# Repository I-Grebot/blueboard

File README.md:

# BlueBoard v1

The BlueBoard is a small form-factor "all-in-one" electronic board for 2 wheels robots.

## Features

The board features the following items:

* Compact size: 10 cm x 10 cm
* Single input power-supply (+14V min)
* Integrated Power-Supplies for logic domains using efficient DC/DC step-down regulators:
 * +12V/1A (industrial sensors)
 * +5V/1A (quadrature encoders, other 5V logic)
 * +3/3V/1A (most of digital logic)
* Integrated  Power-Supplies for heavy loads:
 * +12V/3A (generic purpose)
 * +7.4V/3A (dynamixel digital servos ~ can be adjusted)
 * +5V/3A (analog servos)
* Secure and robust Power-pack connector
* Main ON/OFF + Emergency switch connectors
* 2x Full H-Bridge output controls for DRV8842 (2.5A)
* 8x Opto-coupled analog-servos interface (PWM)
* 2x Connectors + 1x terminal for XL-320 digital servos interface
* 2x Quadrature encoders inputs
* 10x Opto-coupled Industrial sensor inputs (NPN/PNP  types selectable)
* 8x Digital Inputs
* RS485 connector for sensor-bus (to be used with ProxTof boards or other)
* UART with RTS/CTS signals
* USB 2.0 OTG connector
* ST-Link with SWD + SWO programming / debugging connector
* Expander connector (to be used with microBoard_HMI):
 * 1x SPI
 * 1x CAN
 * 6x Digital inputs (user selections switches)
 * 1x Digital outputs 

## Troubleshooting

* Mimimum input voltage (TEN / PTN modules) is high for 4S batteries (error due to 6S -> 4S design migration)
* Not working 4S battery cell monitoring analog circuit (to be further checked)

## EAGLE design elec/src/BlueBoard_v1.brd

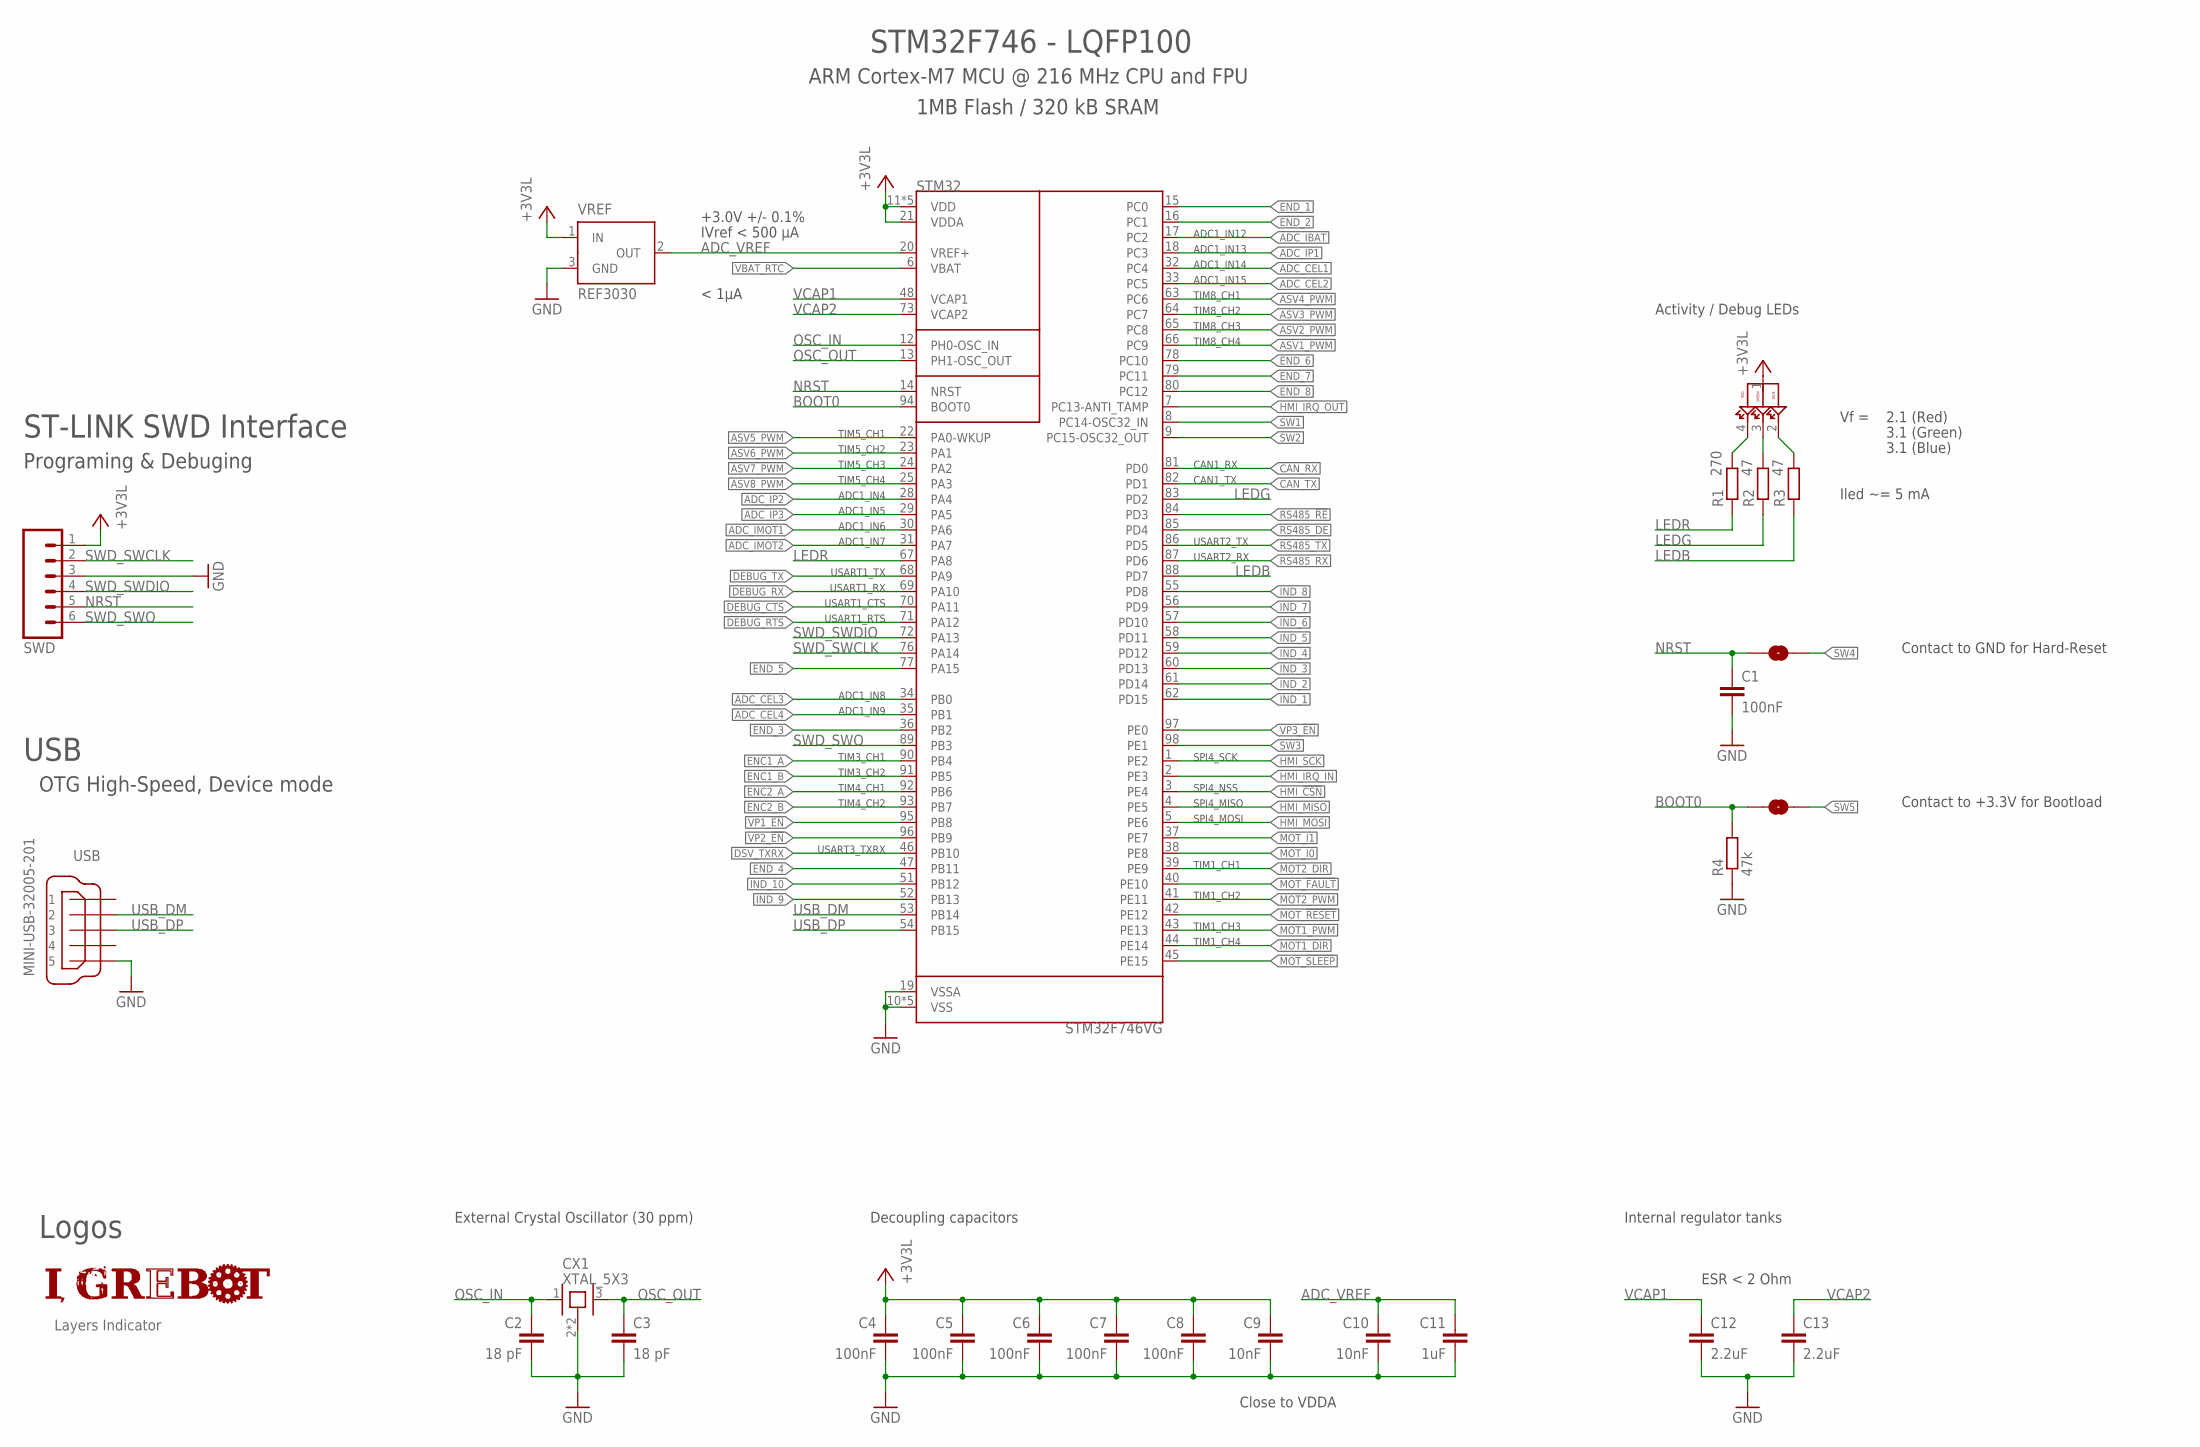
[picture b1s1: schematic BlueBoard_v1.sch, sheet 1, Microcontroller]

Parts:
C1, C4, C5, C6, C7, C8: 100nF; C0603
C2, C3: 18 pF; C0603
C9, C10: 10nF; C0603
C11: 1uF; C0805
C12, C13: 2.2uF; C0805
CX1: XTAL_5X3; CRYSTAL-OSC-SMD-5X3
LED1: ASMB-MTB0-0A3A2; PLCC4
LOGO_IGREBOT: LOGO_IGREBOT12X2MM; IGREBOT_12X2MM
LOGO_LAYERS: LAYERS_CHECK4_LAYERS; LAYERS_CHECK_4
R1: 270; R0603
R2, R3: 47; R0603
R4: 47k; R0603
SJ1, SJ2: SOLDERJUMPERNC2; SJ_2S-NOTRACE
STM32: STM32F746VG; LQFP_100
SWD: M06LOCK; 1X06_LOCK
USB: MINI-USB-32005-201; 32005-201
VREF: REF3030; SOT23

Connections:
+3V3L: C4.1, C5.1, C6.1, C7.1, C8.1, C9.1, LED1.1 (A), STM32.11 (VDD), STM32.21 (VDDA), STM32.27 (VDD), STM32.50 (VDD), STM32.75 (VDD), STM32.100 (VDD), SWD.1, VREF.1 (IN); also elsewhere on the board
ADC_CEL1: STM32.32 (PC4); also elsewhere on the board
ADC_CEL2: STM32.33 (PC5); also elsewhere on the board
ADC_CEL3: STM32.34 (PB0); also elsewhere on the board
ADC_CEL4: STM32.35 (PB1); also elsewhere on the board
ADC_IBAT: STM32.17 (PC2); also elsewhere on the board
ADC_IMOT1: STM32.30 (PA6); also elsewhere on the board
ADC_IMOT2: STM32.31 (PA7); also elsewhere on the board
ADC_IP1: STM32.18 (PC3); also elsewhere on the board
ADC_IP2: STM32.28 (PA4); also elsewhere on the board
ADC_IP3: STM32.29 (PA5); also elsewhere on the board
ADC_VREF: C10.1, C11.1, STM32.20 (VREF+), VREF.2 (OUT)
ASV1_PWM: STM32.66 (PC9); also elsewhere on the board
ASV2_PWM: STM32.65 (PC8); also elsewhere on the board
ASV3_PWM: STM32.64 (PC7); also elsewhere on the board
ASV4_PWM: STM32.63 (PC6); also elsewhere on the board
ASV5_PWM: STM32.22 (PA0-WKUP); also elsewhere on the board
ASV6_PWM: STM32.23 (PA1); also elsewhere on the board
ASV7_PWM: STM32.24 (PA2); also elsewhere on the board
ASV8_PWM: STM32.25 (PA3); also elsewhere on the board
BOOT0: R4.2, SJ2.1, STM32.94 (BOOT0)
CAN_RX: STM32.81 (PD0); also elsewhere on the board
CAN_TX: STM32.82 (PD1); also elsewhere on the board
DEBUG_CTS: STM32.70 (PA11); also elsewhere on the board
DEBUG_RTS: STM32.71 (PA12); also elsewhere on the board
DEBUG_RX: STM32.69 (PA10); also elsewhere on the board
DEBUG_TX: STM32.68 (PA9); also elsewhere on the board
DSV_TXRX: STM32.46 (PB10); also elsewhere on the board
ENC1_A: STM32.90 (PB4); also elsewhere on the board
ENC1_B: STM32.91 (PB5); also elsewhere on the board
ENC2_A: STM32.92 (PB6); also elsewhere on the board
ENC2_B: STM32.93 (PB7); also elsewhere on the board
END_1: STM32.15 (PC0); also elsewhere on the board
END_2: STM32.16 (PC1); also elsewhere on the board
END_3: STM32.36 (PB2); also elsewhere on the board
END_4: STM32.47 (PB11); also elsewhere on the board
END_5: STM32.77 (PA15); also elsewhere on the board
END_6: STM32.78 (PC10); also elsewhere on the board
END_7: STM32.79 (PC11); also elsewhere on the board
END_8: STM32.80 (PC12); also elsewhere on the board
GND: C1.2, C2.2, C3.2, C4.2, C5.2, C6.2, C7.2, C8.2, C9.2, C10.2, C11.2, C12.2, C13.2, CX1.2, CX1.4, R4.1, STM32.10 (VSS), STM32.19 (VSSA), STM32.26 (VSS), STM32.49 (VSS), STM32.74 (VSS), STM32.99 (VSS), SWD.3, USB.5, VREF.3 (GND); also elsewhere on the board
HMI_!CSN!: STM32.3 (PE4); also elsewhere on the board
HMI_IRQ_IN: STM32.2 (PE3); also elsewhere on the board
HMI_IRQ_OUT: STM32.7 (PC13-ANTI_TAMP); also elsewhere on the board
HMI_MISO: STM32.4 (PE5); also elsewhere on the board
HMI_MOSI: STM32.5 (PE6); also elsewhere on the board
HMI_SCK: STM32.1 (PE2); also elsewhere on the board
IND_1: STM32.62 (PD15); also elsewhere on the board
IND_2: STM32.61 (PD14); also elsewhere on the board
IND_3: STM32.60 (PD13); also elsewhere on the board
IND_4: STM32.59 (PD12); also elsewhere on the board
IND_5: STM32.58 (PD11); also elsewhere on the board
IND_6: STM32.57 (PD10); also elsewhere on the board
IND_7: STM32.56 (PD9); also elsewhere on the board
IND_8: STM32.55 (PD8); also elsewhere on the board
IND_9: STM32.52 (PB13); also elsewhere on the board
IND_10: STM32.51 (PB12); also elsewhere on the board
LEDB: R3.1, STM32.88 (PD7)
LEDG: R2.1, STM32.83 (PD2)
LEDR: R1.1, STM32.67 (PA8)
MOT1_DIR: STM32.44 (PE14); also elsewhere on the board
MOT1_PWM: STM32.43 (PE13); also elsewhere on the board
MOT2_DIR: STM32.39 (PE9); also elsewhere on the board
MOT2_PWM: STM32.41 (PE11); also elsewhere on the board
MOT_!FAULT!: STM32.40 (PE10); also elsewhere on the board
MOT_!RESET!: STM32.42 (PE12); also elsewhere on the board
MOT_!SLEEP!: STM32.45 (PE15); also elsewhere on the board
MOT_I0: STM32.38 (PE8); also elsewhere on the board
MOT_I1: STM32.37 (PE7); also elsewhere on the board
unnamed: LED1.4 (CR), R1.2
unnamed: LED1.3 (CG), R2.2
unnamed: LED1.2 (CB), R3.2
NRST: C1.1, SJ1.1, STM32.14 (NRST), SWD.5
OSC_IN: C2.1, CX1.1, STM32.12 (PH0-OSC_IN)
OSC_OUT: C3.1, CX1.3, STM32.13 (PH1-OSC_OUT)
RS485_!RE!: STM32.84 (PD3); also elsewhere on the board
RS485_DE: STM32.85 (PD4); also elsewhere on the board
RS485_RX: STM32.87 (PD6); also elsewhere on the board
RS485_TX: STM32.86 (PD5); also elsewhere on the board
SW1: STM32.8 (PC14-OSC32_IN); also elsewhere on the board
SW2: STM32.9 (PC15-OSC32_OUT); also elsewhere on the board
SW3: STM32.98 (PE1); also elsewhere on the board
SW4: SJ1.2; also elsewhere on the board
SW5: SJ2.2; also elsewhere on the board
SWD_SWCLK: STM32.76 (PA14), SWD.2
SWD_SWDIO: STM32.72 (PA13), SWD.4
SWD_SWO: STM32.89 (PB3), SWD.6
USB_DM: STM32.53 (PB14), USB.2
USB_DP: STM32.54 (PB15), USB.3
VBAT_RTC: STM32.6 (VBAT); also elsewhere on the board
VCAP1: C12.1, STM32.48 (VCAP1)
VCAP2: C13.1, STM32.73 (VCAP2)
VP1_!EN!: STM32.95 (PB8); also elsewhere on the board
VP2_!EN!: STM32.96 (PB9); also elsewhere on the board
VP3_!EN!: STM32.97 (PE0); also elsewhere on the board

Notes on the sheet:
Decoupling capacitors
ESR < 2 Ohm
< 1µA
TIM5_CH1
TIM5_CH2
TIM5_CH3
TIM5_CH4
USART1_TX
USART1_RX
USART1_CTS
USART1_RTS
TIM3_CH1
TIM3_CH2
TIM4_CH1
TIM4_CH2
USART3_TXRX
TIM1_CH4
TIM1_CH3
TIM1_CH2
TIM1_CH1
SPI4_MOSI
SPI4_MISO
SPI4_NSS
SPI4_SCK
USART2_RX
USART2_TX
CAN1_TX
CAN1_RX
TIM8_CH1
TIM8_CH2
TIM8_CH3
TIM8_CH4
USB
Programing & Debuging
ST-LINK SWD Interface
STM32F746 - LQFP100
ARM Cortex-M7 MCU @ 216 MHz CPU and FPU
1MB Flash / 320 kB SRAM
OTG High-Speed, Device mode
Internal regulator tanks

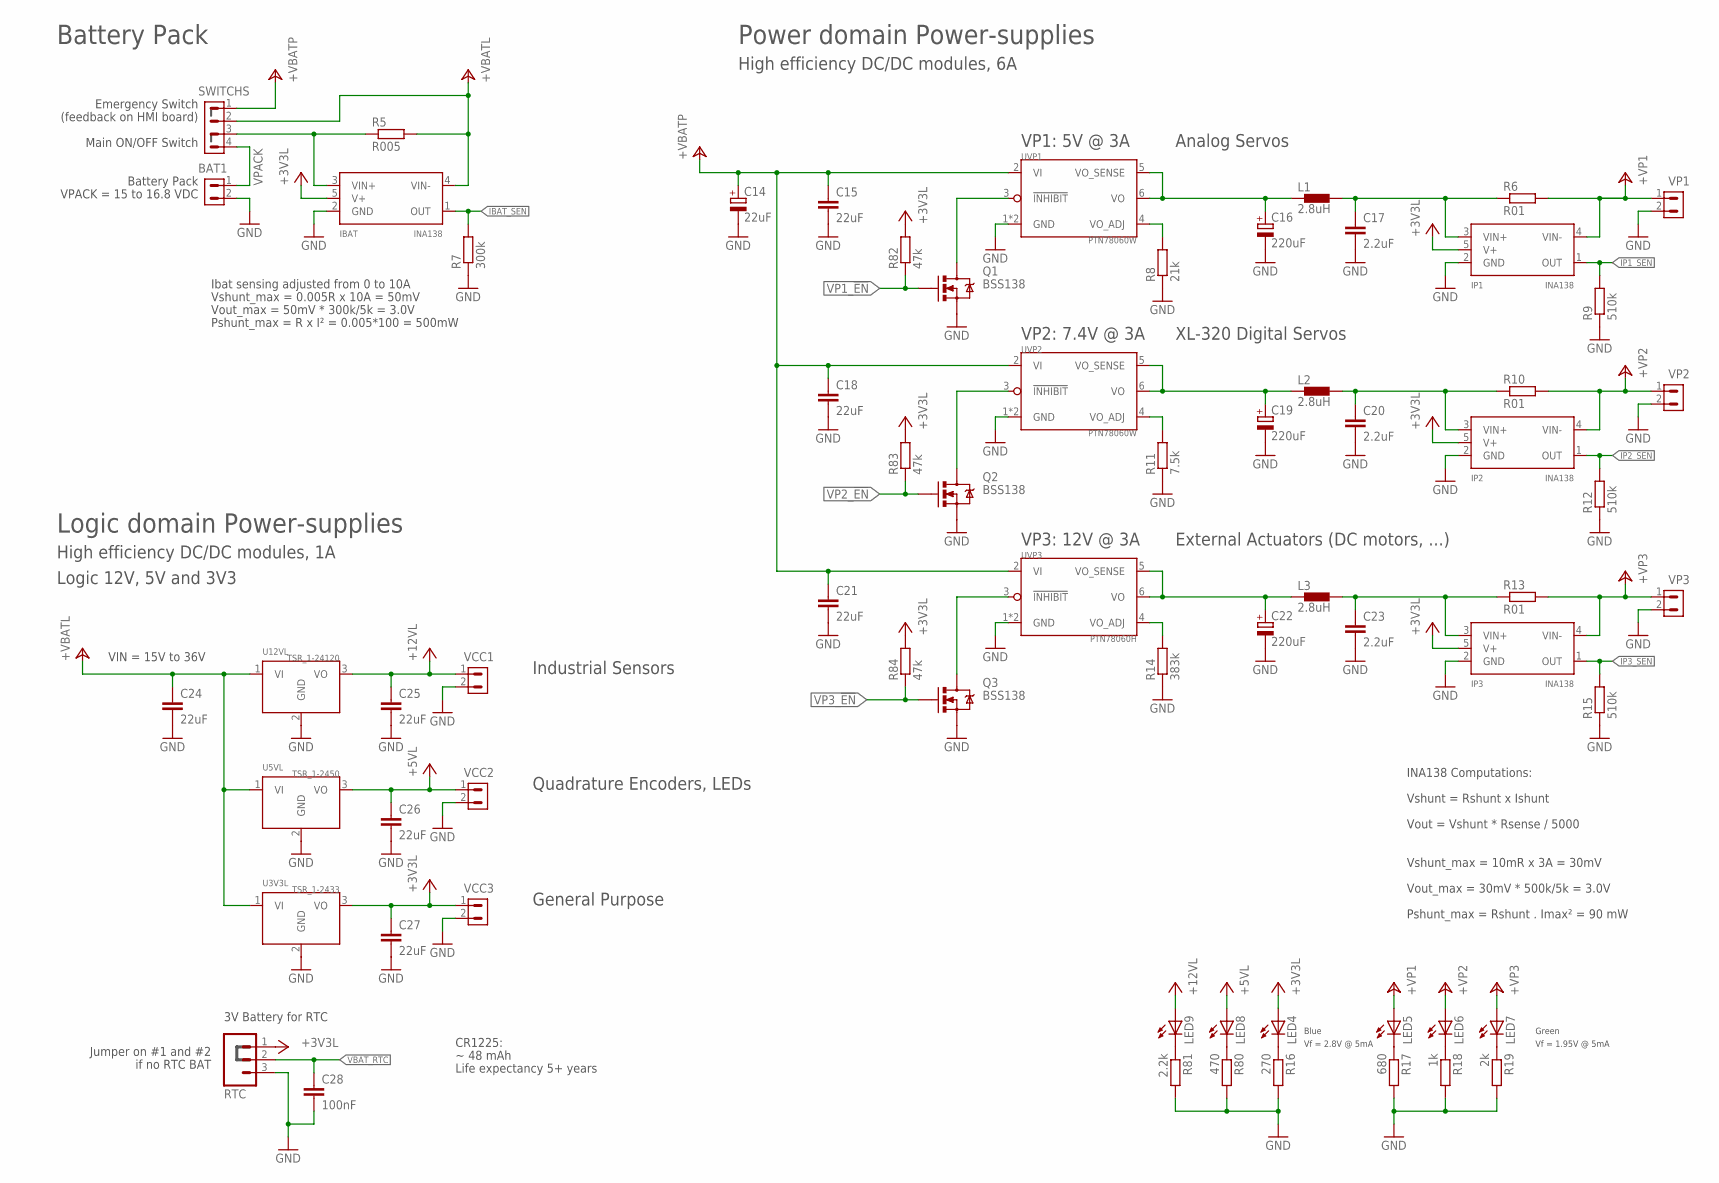
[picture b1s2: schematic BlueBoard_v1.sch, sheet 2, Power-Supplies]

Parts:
BAT1: MC15-GF-3.81-LR_2; CON_3.81_LR_2
C14: 22uF; PANASONIC_B
C15, C18, C21, C24: 22uF; C3225
C16, C19, C22: 220uF; PANASONIC_D
C17, C20, C23: 2.2uF; C3225
C25, C26, C27: 22uF; C1210
C28: 100nF; C0603
IBAT: INA138; DBV_05
IP1, IP2, IP3: INA138; DBV_05
L1, L2, L3: 2.8uH; DR1030
LED4, LED5, LED6, LED7, LED8, LED9: LEDCHIP-LED0805; CHIP-LED0805
Q1, Q2, Q3: BSS138; SOT23
R5: R005; R2512
R6, R10, R13: R01; R2512
R7: 300k; R0603
R8: 21k; R0603
R9, R12, R15: 510k; R0603
R11: 7.5k; R0603
R14: 383k; R0603
R16: 270; R0603
R17: 680; R0603
R18: 1k; R0603
R19: 2k; R0603
R80: 470; R0603
R81: 2.2k; R0603
R82, R83, R84: 47k; R0603
RTC: M03LOCK; 1X03_LOCK
SWITCHS: MC15-GF-3.81-LR_4; CON_3.81_LR_4
U3V3L: TSR_1-2433; TSR1
U5VL: TSR_1-2450; TSR1
U12VL: TSR_1-24120; TSR1
UVP1, UVP2: PTN78060W; PTN78060
UVP3: PTN78060H; PTN78060
VCC1, VCC2, VCC3: CON_3.5_2
VP1, VP2, VP3: CON_3.5_2

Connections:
!INHIBIT!_VP1: Q1.3 (D), UVP1.3 (!INHIBIT!)
!INHIBIT!_VP5: Q2.3 (D), UVP2.3 (!INHIBIT!)
!INHIBIT!_VP6: Q3.3 (D), UVP3.3 (!INHIBIT!)
+3V3L: C27.1, IBAT.5 (V+), IP1.5 (V+), IP2.5 (V+), IP3.5 (V+), LED4.A, R82.2, R83.2, R84.2, RTC.1, U3V3L.3 (VO), VCC3.1; also elsewhere on the board
+5VL: C26.1, LED8.A, U5VL.3 (VO), VCC2.1; also elsewhere on the board
+12VL: C25.1, LED9.A, U12VL.3 (VO), VCC1.1; also elsewhere on the board
+VBATL: C24.1, IBAT.4 (VIN-), R5.2, SWITCHS.2, U3V3L.1 (VI), U5VL.1 (VI), U12VL.1 (VI)
+VBATP: C14.+, C15.1, C18.1, C21.1, SWITCHS.1, UVP1.2 (VI), UVP2.2 (VI), UVP3.2 (VI); also elsewhere on the board
+VP1: IP1.4 (VIN-), LED5.A, R6.2, VP1.1; also elsewhere on the board
+VP2: IP2.4 (VIN-), LED6.A, R10.2, VP2.1; also elsewhere on the board
+VP3: IP3.4 (VIN-), LED7.A, R13.2, VP3.1
GND: BAT1.2, C14.-, C15.2, C16.-, C17.2, C18.2, C19.-, C20.2, C21.2, C22.-, C23.2, C24.2, C25.2, C26.2, C27.2, C28.2, IBAT.2 (GND), IP1.2 (GND), IP2.2 (GND), IP3.2 (GND), Q1.2 (S), Q2.2 (S), Q3.2 (S), R7.1, R8.1, R9.1, R11.1, R12.1, R14.1, R15.1, R16.2, R17.2, R18.2, R19.2, R80.2, R81.2, RTC.3, U3V3L.2 (GND), U5VL.2 (GND), U12VL.2 (GND), UVP1.1 (GND), UVP1.7 (GND), UVP2.1 (GND), UVP2.7 (GND), UVP3.1 (GND), UVP3.7 (GND), VCC1.2, VCC2.2, VCC3.2, VP1.2, VP2.2, VP3.2; also elsewhere on the board
IBAT_SEN: IBAT.1 (OUT), R7.2; also elsewhere on the board
IP1_SEN: IP1.1 (OUT), R9.2; also elsewhere on the board
IP2_SEN: IP2.1 (OUT), R12.2; also elsewhere on the board
IP3_SEN: IP3.1 (OUT), R15.2; also elsewhere on the board
unnamed: C16.+, L1.1, UVP1.5 (VO_SENSE), UVP1.6 (VO)
unnamed: C17.1, IP1.3 (VIN+), L1.2, R6.1
unnamed: R14.2, UVP3.4 (VO_ADJ)
unnamed: R11.2, UVP2.4 (VO_ADJ)
unnamed: C19.+, L2.1, UVP2.5 (VO_SENSE), UVP2.6 (VO)
unnamed: R8.2, UVP1.4 (VO_ADJ)
unnamed: C20.1, IP2.3 (VIN+), L2.2, R10.1
unnamed: C22.+, L3.1, UVP3.5 (VO_SENSE), UVP3.6 (VO)
unnamed: C23.1, IP3.3 (VIN+), L3.2, R13.1
unnamed: LED8.C, R80.1
unnamed: LED9.C, R81.1
unnamed: LED5.C, R17.1
unnamed: LED4.C, R16.1
unnamed: LED6.C, R18.1
unnamed: LED7.C, R19.1
unnamed: IBAT.3 (VIN+), R5.1, SWITCHS.3
VBAT_RTC: C28.1, RTC.2; also elsewhere on the board
VP1_!EN!: Q1.1 (G), R82.1; also elsewhere on the board
VP2_!EN!: Q2.1 (G), R83.1; also elsewhere on the board
VP3_!EN!: Q3.1 (G), R84.1; also elsewhere on the board
VPACK: BAT1.1, SWITCHS.4

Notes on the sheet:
VP1: 5V @ 3A
VP2: 7.4V @ 3A
Logic 12V, 5V and 3V3
VPACK = 15 to 16.8 VDC
Logic domain Power-supplies
High efficiency DC/DC modules, 1A
Power domain Power-supplies
High efficiency DC/DC modules, 6A
Battery Pack
Vshunt = Rshunt x Ishunt
Vout = Vshunt * Rsense / 5000
Vshunt_max = 10mR x 3A = 30mV
Vout_max = 30mV * 500k/5k = 3.0V
Emergency Switch
Main ON/OFF Switch
(feedback on HMI board)
Vshunt_max = 0.005R x 10A = 50mV
Vout_max = 50mV * 300k/5k = 3.0V
Ibat sensing adjusted from 0 to 10A
INA138 Computations:
Pshunt_max = R x I² = 0.005*100 = 500mW
Analog Servos
XL-320 Digital Servos
Industrial Sensors
General Purpose
Quadrature Encoders, LEDs
VP3: 12V @ 3A
External Actuators (DC motors, ...)
3V Battery for RTC
~ 48 mAh
Life expectancy 5+ years
Green
Blue
CR1225:
Pshunt_max = Rshunt . Imax² = 90 mW
Jumper on #1 and #2
if no RTC BAT
Vf = 2.8V @ 5mA
Vf = 1.95V @ 5mA
VIN = 15V to 36V

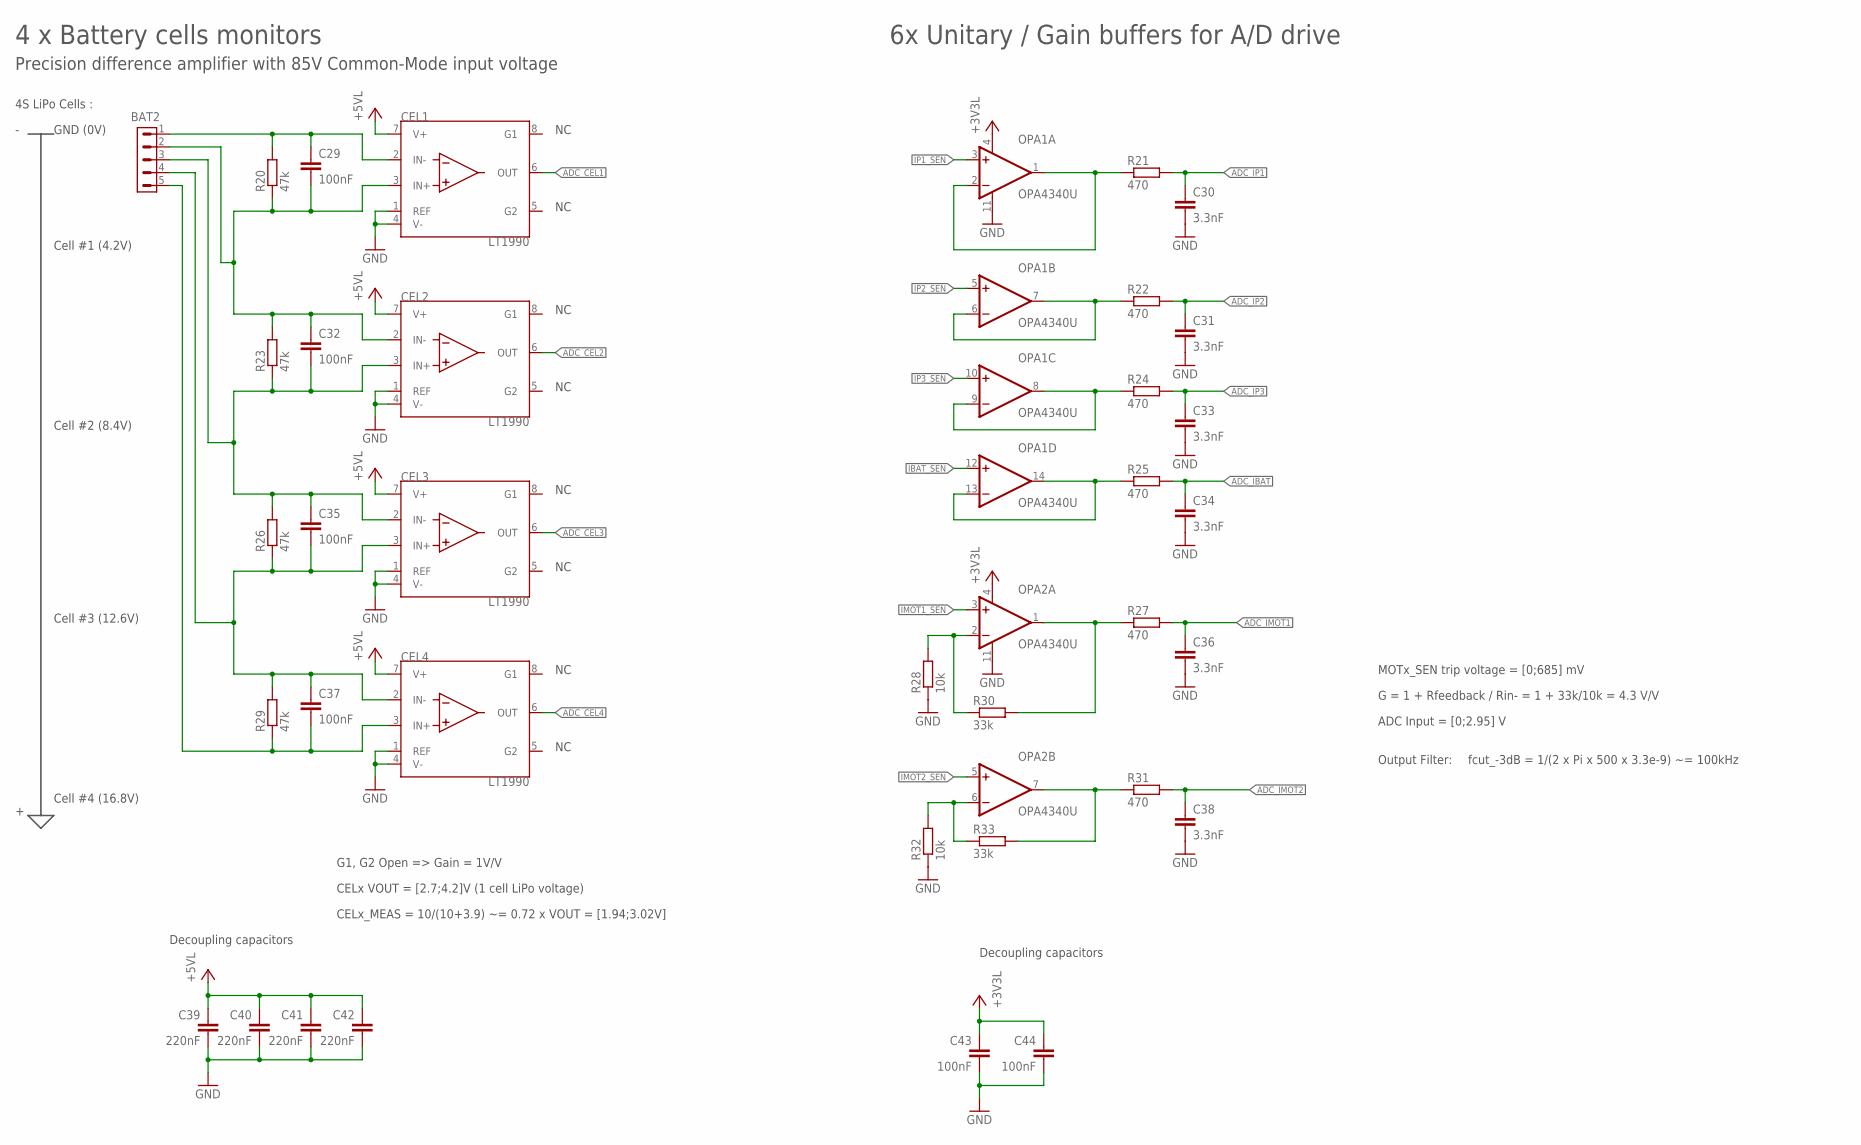
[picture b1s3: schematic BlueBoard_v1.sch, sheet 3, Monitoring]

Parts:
BAT2: JST-XH-S_5; JST-XH-5S
C29, C32, C35, C37, C43, C44: 100nF; C0603
C30, C31, C33, C34, C36, C38: 3.3nF; C0603
C39, C40, C41, C42: 220nF; C0603
CEL1, CEL2, CEL3, CEL4: LT1990; S8
OPA1, OPA2: OPA4340U; SO14
R20, R23, R26, R29: 47k; R0603
R21, R22, R24, R25, R27, R31: 470; R0603
R28, R32: 10k; R0603
R30, R33: 33k; R0603

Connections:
+3V3L: C43.1, C44.1, OPA1.4 (V+), OPA2.4 (V+); also elsewhere on the board
+5VL: C39.1, C40.1, C41.1, C42.1, CEL1.7 (V+), CEL2.7 (V+), CEL3.7 (V+), CEL4.7 (V+); also elsewhere on the board
ADC_CEL1: CEL1.6 (OUT); also elsewhere on the board
ADC_CEL2: CEL2.6 (OUT); also elsewhere on the board
ADC_CEL3: CEL3.6 (OUT); also elsewhere on the board
ADC_CEL4: CEL4.6 (OUT); also elsewhere on the board
ADC_IBAT: C34.1, R25.2; also elsewhere on the board
ADC_IMOT1: C36.1, R27.2; also elsewhere on the board
ADC_IMOT2: C38.1, R31.2; also elsewhere on the board
ADC_IP1: C30.1, R21.2; also elsewhere on the board
ADC_IP2: C31.1, R22.2; also elsewhere on the board
ADC_IP3: C33.1, R24.2; also elsewhere on the board
GND: C30.2, C31.2, C33.2, C34.2, C36.2, C38.2, C39.2, C40.2, C41.2, C42.2, C43.2, C44.2, CEL1.1 (REF), CEL1.4 (V-), CEL2.1 (REF), CEL2.4 (V-), CEL3.1 (REF), CEL3.4 (V-), CEL4.1 (REF), CEL4.4 (V-), OPA1.11 (V-), OPA2.11 (V-), R28.1, R32.1; also elsewhere on the board
IBAT_SEN: OPA1.12 (+IN); also elsewhere on the board
IMOT1_SEN: OPA2.3 (+IN); also elsewhere on the board
IMOT2_SEN: OPA2.5 (+IN); also elsewhere on the board
IP1_SEN: OPA1.3 (+IN); also elsewhere on the board
IP2_SEN: OPA1.5 (+IN); also elsewhere on the board
IP3_SEN: OPA1.10 (+IN); also elsewhere on the board
unnamed: OPA2.2 (-IN), R28.2, R30.1
unnamed: OPA2.6 (-IN), R32.2, R33.1
unnamed: OPA1.1 (OUT), OPA1.2 (-IN), R21.1
unnamed: OPA1.6 (-IN), OPA1.7 (OUT), R22.1
unnamed: OPA1.8 (OUT), OPA1.9 (-IN), R24.1
unnamed: OPA1.13 (-IN), OPA1.14 (OUT), R25.1
unnamed: OPA2.1 (OUT), R27.1, R30.2
unnamed: OPA2.7 (OUT), R31.1, R33.2
unnamed: BAT2.1, C29.1, CEL1.2 (IN-), R20.2
unnamed: BAT2.2, C29.2, C32.1, CEL1.3 (IN+), CEL2.2 (IN-), R20.1, R23.2
unnamed: BAT2.3, C32.2, C35.1, CEL2.3 (IN+), CEL3.2 (IN-), R23.1, R26.2
unnamed: BAT2.4, C35.2, C37.1, CEL3.3 (IN+), CEL4.2 (IN-), R26.1, R29.2
unnamed: BAT2.5, C37.2, CEL4.3 (IN+), R29.1

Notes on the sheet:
G1, G2 Open => Gain = 1V/V
CELx VOUT = [2.7;4.2]V (1 cell LiPo voltage)
CELx_MEAS = 10/(10+3.9) ~= 0.72 x VOUT = [1.94;3.02V]
4S LiPo Cells :
GND (0V)
Cell #1 (4.2V)
Cell #2 (8.4V)
Cell #3 (12.6V)
Cell #4 (16.8V)
4 x Battery cells monitors
Precision difference amplifier with 85V Common-Mode input voltage
fcut_-3dB = 1/(2 x Pi x 500 x 3.3e-9) ~= 100kHz
G = 1 + Rfeedback / Rin- = 1 + 33k/10k = 4.3 V/V
MOTx_SEN trip voltage = [0;685] mV
ADC Input = [0;2.95] V
6x Unitary / Gain buffers for A/D drive
Decoupling capacitors
Output Filter:

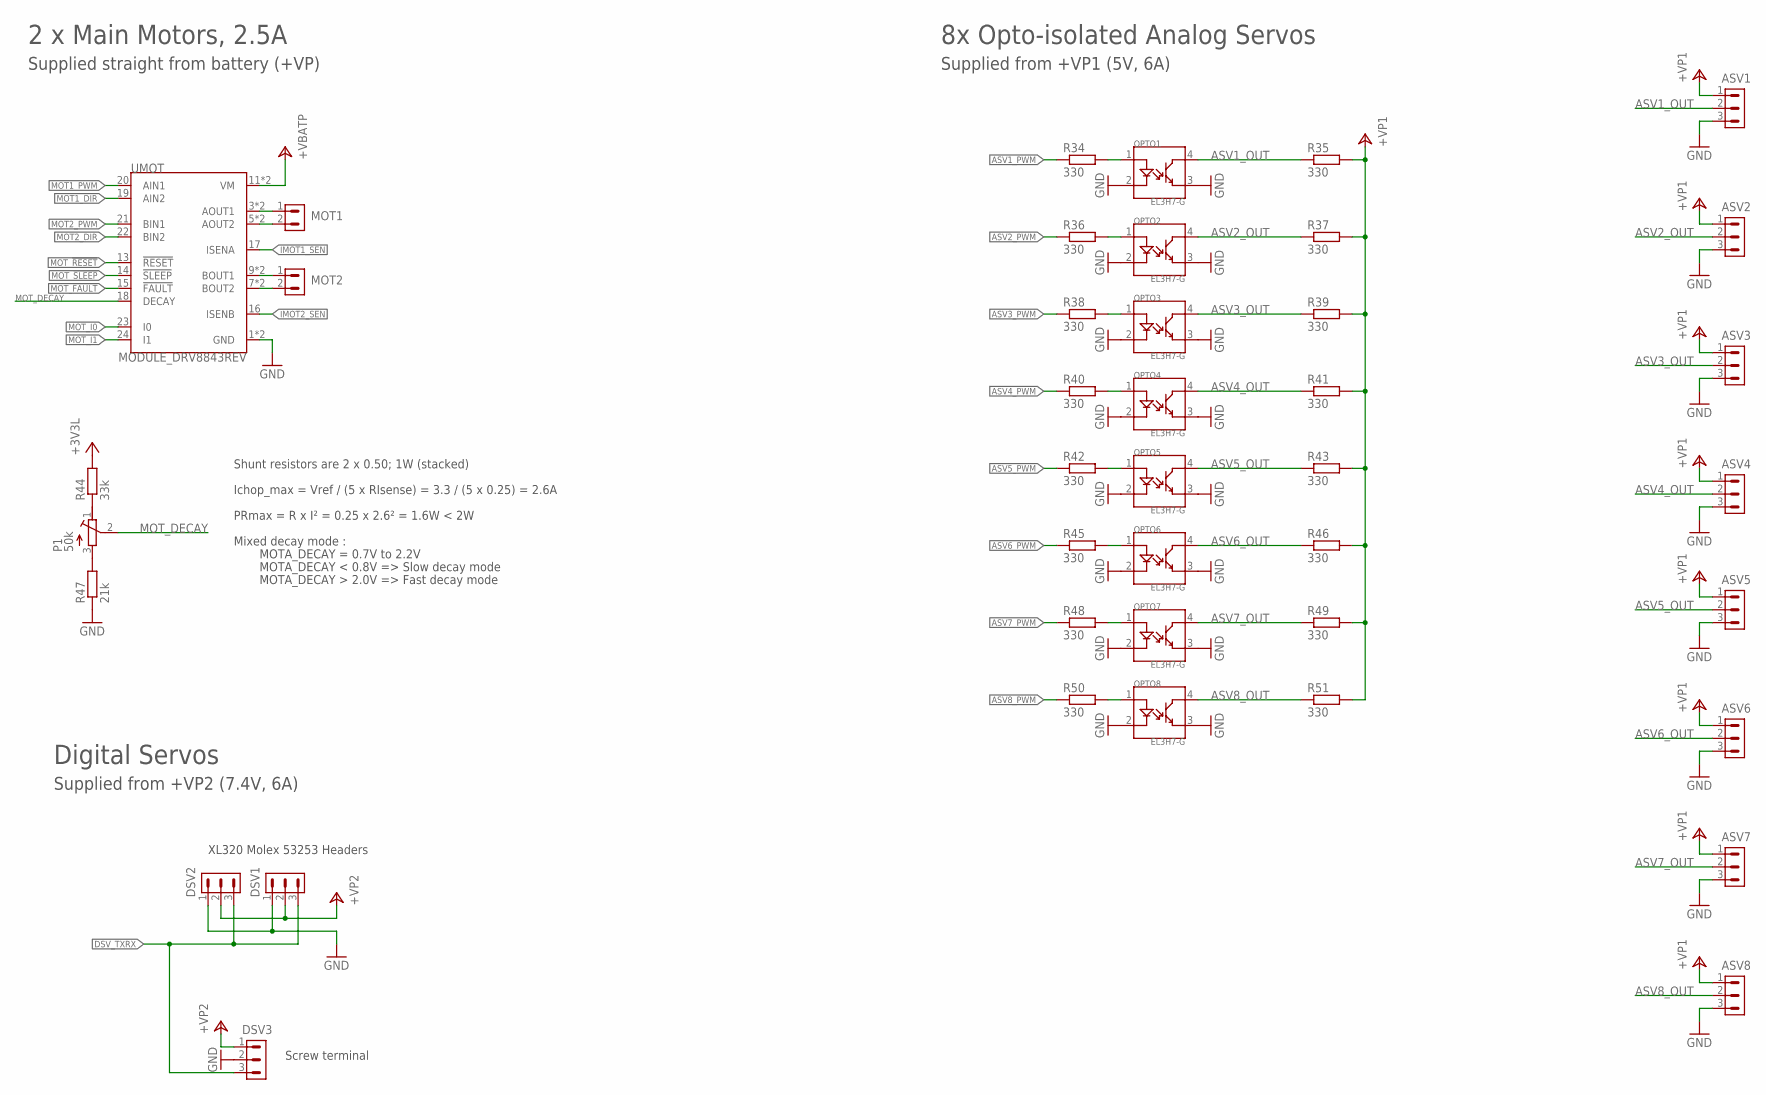
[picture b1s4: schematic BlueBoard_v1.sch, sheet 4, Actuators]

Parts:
ASV1, ASV2, ASV3, ASV4, ASV5, ASV6, ASV7, ASV8: CON_3.5_3
DSV1, DSV2: CON_2.00_MOLEX-53253_3
DSV3: CON_3.5_3
MOT1, MOT2: CON_3.5_2
OPTO1, OPTO2, OPTO3, OPTO4, OPTO5, OPTO6, OPTO7, OPTO8: EL3H7-G; SSOP_4
P1: 50k; RTRIMT93XB
R34, R35, R36, R37, R38, R39, R40, R41, R42, R43, R45, R46, R48, R49, R50, R51: 330; R0603
R44: 33k; R0603
R47: 21k; R0603
UMOT: MODULE_DRV8843REV; MODULE_DRV884X_REV

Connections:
+3V3L: R44.2; also elsewhere on the board
+VBATP: UMOT.11 (VM), UMOT.12 (VM); also elsewhere on the board
+VP1: ASV1.1, ASV2.1, ASV3.1, ASV4.1, ASV5.1, ASV6.1, ASV7.1, ASV8.1, R35.2, R37.2, R39.2, R41.2, R43.2, R46.2, R49.2, R51.2; also elsewhere on the board
+VP2: DSV1.2, DSV2.2, DSV3.1; also elsewhere on the board
ASV1_OUT: ASV1.2, OPTO1.4, R35.1
ASV1_PWM: R34.1; also elsewhere on the board
ASV2_OUT: ASV2.2, OPTO2.4, R37.1
ASV2_PWM: R36.1; also elsewhere on the board
ASV3_OUT: ASV3.2, OPTO3.4, R39.1
ASV3_PWM: R38.1; also elsewhere on the board
ASV4_OUT: ASV4.2, OPTO4.4, R41.1
ASV4_PWM: R40.1; also elsewhere on the board
ASV5_OUT: ASV5.2, OPTO5.4, R43.1
ASV5_PWM: R42.1; also elsewhere on the board
ASV6_OUT: ASV6.2, OPTO6.4, R46.1
ASV6_PWM: R45.1; also elsewhere on the board
ASV7_OUT: ASV7.2, OPTO7.4, R49.1
ASV7_PWM: R48.1; also elsewhere on the board
ASV8_OUT: ASV8.2, OPTO8.4, R51.1
ASV8_PWM: R50.1; also elsewhere on the board
DSV_TXRX: DSV1.3, DSV2.3, DSV3.3; also elsewhere on the board
GND: ASV1.3, ASV2.3, ASV3.3, ASV4.3, ASV5.3, ASV6.3, ASV7.3, ASV8.3, DSV1.1, DSV2.1, DSV3.2, OPTO1.2, OPTO1.3, OPTO2.2, OPTO2.3, OPTO3.2, OPTO3.3, OPTO4.2, OPTO4.3, OPTO5.2, OPTO5.3, OPTO6.2, OPTO6.3, OPTO7.2, OPTO7.3, OPTO8.2, OPTO8.3, R47.1, UMOT.1 (GND), UMOT.2 (GND); also elsewhere on the board
IMOT1_SEN: UMOT.17 (ISENA); also elsewhere on the board
IMOT2_SEN: UMOT.16 (ISENB); also elsewhere on the board
MOT1_DIR: UMOT.19 (AIN2); also elsewhere on the board
MOT1_PWM: UMOT.20 (AIN1); also elsewhere on the board
MOT2_DIR: UMOT.22 (BIN2); also elsewhere on the board
MOT2_PWM: UMOT.21 (BIN1); also elsewhere on the board
MOT_!FAULT!: UMOT.15 (!FAULT!); also elsewhere on the board
MOT_!RESET!: UMOT.13 (!RESET!); also elsewhere on the board
MOT_!SLEEP!: UMOT.14 (!SLEEP!); also elsewhere on the board
MOT_DECAY: P1.2 (S), UMOT.18 (DECAY)
MOT_I0: UMOT.23 (I0); also elsewhere on the board
MOT_I1: UMOT.24 (I1); also elsewhere on the board
unnamed: OPTO1.1, R34.2
unnamed: OPTO2.1, R36.2
unnamed: OPTO3.1, R38.2
unnamed: OPTO4.1, R40.2
unnamed: OPTO5.1, R42.2
unnamed: OPTO6.1, R45.2
unnamed: OPTO7.1, R48.2
unnamed: OPTO8.1, R50.2
unnamed: MOT1.1, UMOT.3 (AOUT1), UMOT.4 (AOUT1)
unnamed: MOT1.2, UMOT.5 (AOUT2), UMOT.6 (AOUT2)
unnamed: MOT2.1, UMOT.9 (BOUT1), UMOT.10 (BOUT1)
unnamed: MOT2.2, UMOT.7 (BOUT2), UMOT.8 (BOUT2)
unnamed: P1.3 (E), R47.2
unnamed: P1.1 (A), R44.1

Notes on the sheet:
2 x Main Motors, 2.5A
Ichop_max = Vref / (5 x RIsense) = 3.3 / (5 x 0.25) = 2.6A
PRmax = R x I² = 0.25 x 2.6² = 1.6W < 2W
Shunt resistors are 2 x 0.50; 1W (stacked)
Supplied straight from battery (+VP)
Mixed decay mode :
MOTA_DECAY = 0.7V to 2.2V
MOTA_DECAY < 0.8V => Slow decay mode
MOTA_DECAY > 2.0V => Fast decay mode
8x Opto-isolated Analog Servos
Supplied from +VP1 (5V, 6A)
Digital Servos
Supplied from +VP2 (7.4V, 6A)
Screw terminal
XL320 Molex 53253 Headers

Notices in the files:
parts and their libraries:
SparkFun-DiscreteSemi: Licensing: Creative Commons ShareAlike 4.0 International - https://creativecommons.org/licenses/by-sa/4.0
